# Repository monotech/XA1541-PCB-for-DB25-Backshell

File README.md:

# XA1541-PCB-for-DB25-Backshell
XA1541 Commodore drive/machine to PC parallel port converter cable. PCB for DB25 backshell

Designed to fit the grey plastic DB25 backshells like the Cinch 40-9725H (Digikey 367-1174), and the Connfly DS1045-25AP1S1-A, as well as many generic ones you can find that match those two.

Details about XA1541 is here: http://sta.c64.org/xa1541.html

Credit for schematic goes to Michael Klein and Nicolas Welte, 2000.

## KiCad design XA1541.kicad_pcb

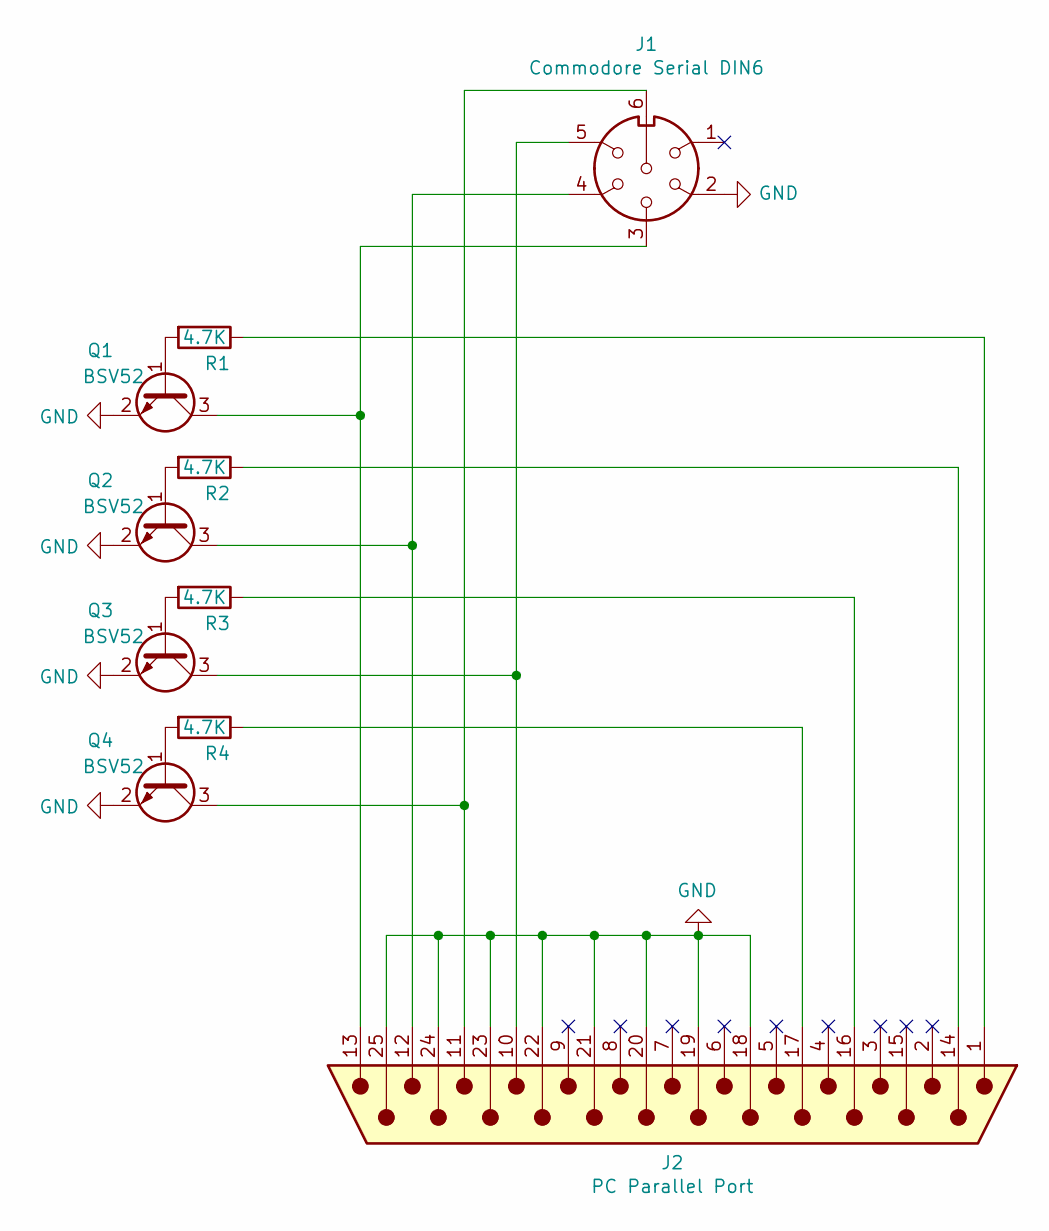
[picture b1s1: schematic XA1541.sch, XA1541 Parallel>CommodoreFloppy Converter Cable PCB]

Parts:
J1: Commodore Serial DIN6; Pin_Header_Angled_1x06_Pitch2.54mm
J2: PC Parallel Port; DSUB-25_Male_EdgeMount_P2.77mm
Q1, Q2, Q3, Q4: BSV52; SOT-23
R1, R2, R3, R4: 4.7K; R_Axial_DIN0204_L3.6mm_D1.6mm_P5.08mm_Horizontal

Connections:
GND: J1.2, J2.18, J2.19, J2.20, J2.21, J2.22, J2.23, J2.24, J2.25, Q1.2 (E), Q2.2 (E), Q3.2 (E), Q4.2 (E)
unnamed: J1.3, J2.13, Q1.3 (C)
unnamed: J1.4, J2.12, Q2.3 (C)
unnamed: J1.5, J2.10, Q3.3 (C)
unnamed: J1.6, J2.11, Q4.3 (C)
unnamed: J2.1, R1.1
unnamed: J2.14, R2.1
unnamed: J2.16, R3.1
unnamed: J2.17, R4.1
unnamed: Q1.1 (B), R1.2
unnamed: Q2.1 (B), R2.2
unnamed: Q3.1 (B), R3.2
unnamed: Q4.1 (B), R4.2

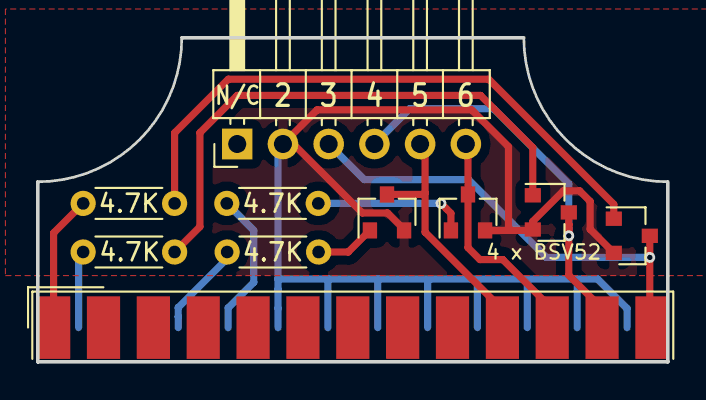
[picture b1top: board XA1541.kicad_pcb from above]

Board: 2 copper layers, 35.0 x 18.0 mm, 10 parts (0 on the bottom side), 13 nets.
